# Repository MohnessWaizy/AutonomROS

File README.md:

# AutonomROS: Autonomous Car Swarm with Hardware-accelerated ROS Programming

## Paper @ IRC-2023:
[Paper: AutonomROS: A ReconROS-based Autonomonous Driving Unit](https://arxiv.org/pdf/2309.02026.pdf)

We present an Ackermann-based autonomous driving robot car based on  an [ROS 2](https://docs.ros.org/en/galactic/index.html) architecture alongside accelerated computationally intensive components using hardware acceleration through [ReconROS](https://github.com/Lien182/ReconROS) on an [Zynq UltraScale+ MPSoC ZCU104](https://www.xilinx.com/products/boards-and-kits/zcu104.html) FPGA board. First, our robot car can drive in a lane at a predefined speed. Second, it can detect obstacles and avoid collisions by stopping. Third, our car prevents intersection collisions with other vehicles by communicating via Wifi to a virtual traffic light offering smooth intersection coordination. Finally, since our developed architecture builds upon [Navigation 2 (Nav2)](https://navigation.ros.org/), a commonly used ROS 2 framework, we provide smooth integration and extendability. Furthermore, we accelerated three computationally intensive architecture components, lane detection, point cloud calculation, and obstacle detection, to save CPU time. In addition, we discovered that leveraging shared memory through [Iceoryx](https://iceoryx.io/latest/) as the ROS 2 middleware further reduced CPU time. Hence, we extended ReconROS’s capabilities by
making it compatible with Iceoryx.

<div align="center">
  
</div>

<div align="center">

</div>

<div align="center">

</div>

## Demo Video

<div align="center">
  
</div>

## Hardware

- Zynq UltraScale+ MPSoC ZCU104
- Traxxas Racecar Slash 2WD
- Ultrasonic Sensor (HC-SR04)
- Hall Sensor (KY-024)
- IMU (BNO055)
- PMOD0 Breakout Board
- 2D-Camera (SeeCam Cu30)
- 3D-Camera (Astra Pro)
- Wifi Sticks (TP Link TL-WN823NV3)
- Powered USB Hub (CSL USB Hub 3.2 Gen1)
- MakerBeams

## Tested on

- Ubuntu 20.04 LTS (Focal Fossa)
- ROS 2 Galactic
- Vivado 2021.2
- amd64 architecture (PC)
- arm64 architecture (ZCU104)

For more detailed information regarding dependencies consider the `ansible` folder

## Installation

### 0. Install git

If git is not already installed on your computer, install it with:

```bash
sudo apt install git
```

### 1. Clone the repository

```bash
git clone git@git.uni-paderborn.de:clienen/autonomros.git
```

### 2. Initialize the submodules

Change into the root of the repository and run the following command:

```bash
git submodule update --init
```

### 3. Initialize environment

We provide a recommended way to install all requirements using Ansible, which might cause changes on your system. Otherwise look into the ansible playbooks and follow the steps manually.

#### 3.1 Install Ansible

You can either run our script `first_install.sh` or look into the documentation of Ansible.
!We do not provide any warranty for potential damages!

```bash
ansible/scripts/first_install.sh
```

#### 3.2 Run Ansible

```bash
source ~/venvs/ansible/bin/activate
cd ansible/
ansible-playbook -i hosts.yml lab.yml -K --extra-vars "main_user_name=YOUR_USERNAME"
```

Exchange `YOUR_USERNAME` with your local username. It is required that you have root access via sudo. The `BECOME password` is your password. You may get an error for the `reconros : Build docker image` step. If this is the case, restart your computer and run the ansible playbook again.

#### 3.3 Install Vivado

Go to [Xilinx website](https://www.xilinx.com/support/download/index.html/content/xilinx/en/downloadNav/vivado-design-tools/2021-2.html) and download  Xilinx Unified Installer 2021.2: Linux Self Extracting Web Installer. Move the file into `~/ansible-files/`. Then run the following commands:

```bash
cd ~/ansible-files/
chmod u+x ./Xilinx_Unified_2021.2_1021_0703_Lin64.bin
./Xilinx_Unified_2021.2_1021_0703_Lin64.bin -- -b AuthTokenGen
```

Here, you will be asked for your Xilinx Account Credentials.
Next, you need to accept the Xilinx EULA and 3rd Party EULA.
The following command accepts the EULAs, downloads, and installs Vivado (this may take some hours):

```bash
~/ansible-files/Xilinx_Unified_2021.2_1021_0703_Lin64.bin -- -b Install -c ~/ansible-files/install_config.txt -a XilinxEULA,3rdPartyEULA
```

#### 3.4 Setup Virtual Traffic Light i.e. Installing mosquitto

To install the Mosquitto broker and the Mosquitto command line tools, run:

```bash
sudo apt-get install mosquitto mosquitto-clients -y
```

The Mosquitto broker starts automatically after installing.

Run the following line to start the Mosquitto broker on each system start:

```bash
sudo systemctl enable mosquitto
```

You need to allow anonymous acces by editing `/etc/mosquitto/mosquitto.conf` and adding:

```
allow_anonymous true
```

Be aware of the security implications!

The mosquitto server must be accessible by the board. You can listen on all interfaces by adding the following to the configuration.

```
listener 1883 0.0.0.0
```

Be aware of the security implications!

#### 3.5 Board Setup

You first need to setup an SD card. For this follow the steps in [board/README.md](board/README.md).

#### 3.6 Computer Setup

Append the following lines to your `.bashrc`:

```bash
source /opt/ros/galactic/setup.bash
export ROS_DOMAIN_ID=53
```

Reopen the terminal.

## Usage

### 1.1 Building the ReconROS project

Before running the commands below switch to the correct folder and source the ReconROS environment.

```bash
cd code/reconros_ws/carcontrol
source ../ReconROS/tools/settings.sh
```

Build the messages (Only necessary in the first setup)

```bash
make build-msg
```

Build the hardware. Make sure you have enough RAM or swap space (at least 32 GB combined are recommended).

```bash
make build-hw
```

Build the software

```bash
make build-sw
```

Copy the necessary files to the board

```bash
make copy
```

Note: Make sure to create an entry in your ssh config `~/.ssh/config` called `board` for the Zynq UltraScale+ MPSoC ZCU104

```bash
Host board
        User xilinx
        HostName BOARD_IP_ADDRESS
```

### 1.2 Building the ROS 2 packages

If you have previously performed the steps in the previous section, reopen the terminal to have a clean environment again.

```bash
cd code/ros_ws
```

Update `rosdep` with:

```bash
rosdep update --include-eol-distros
```

Install the required dependencies:

```bash
make dependencies
```

Build the ROS 2 packages for the board:

```bash
make build-arm64
```

Copy the necessary files to the board:

```bash
make board-copy
```

Update `rosdep` on the board:

```bash
ssh board rosdep update --include-eol-distros
```

Install the required dependencies on the board:

```bash
make board-dependencies
```

Copy the necessary scripts to the board:

```bash
cd code/scripts
make board-copy-scripts
```

### 2. Run with rviz2

Note: If anything crashes (except the `set_camera_config.sh`) rerun the step.

#### 2.1 Setup the rviz2 config

It is advised to use the config for rviz2 provided in [code/ros_ws/src/nav2_local/rviz/config.rviz](code/ros_ws/src/nav2_local/rviz/config.rviz)

Start rviz2 with

```bash
rviz2 -d code/ros_ws/src/nav2_local/rviz/config.rviz
```

#### 2.2 Connect to the board and start Roudi

Connect to the board

```bash
ssh board 
```

Run Roudi

```bash
./roudi.sh
```

#### 2.3 In a new terminal: Load the bitstream onto the FPGA and run the delegate threads

Connect to the board

```bash
ssh board 
```

Go in the directory `carcontrol`

```bash
cd carcontrol
```

Load the bitstream onto the FPGA

```bash
./load_fpga.sh
```

Run the delegate threads

```bash
sudo ./run_software.sh
```

#### 2.4 Start MQTT server for the virtual traffic light

Make sure the MQTT server is running on the computer:

```bash
service mosquitto status
```

#### 2.5 In a new terminal: Start Nav2

Connect to the board

```bash
ssh board
```

Run Nav2

```bash
sudo ./start_nav2.sh
```

Important: Wait until the terminal stops outputting log messages

#### 2.6 In a new terminal: Configure the 2D camera

Connect to the board

```bash
ssh board
```

Run the configuration file

```bash
./set_camera_config.sh
```

Wait approximately 5 seconds and rerun the command:

```bash
./set_camera_config.sh
```

Go back to rviz2 on your local machine and press "Startup" and wait until the terminal running Nav2 stops outputting log messages again. In rvz2 the car and the costmap should be visible at this point.

#### 2.7 In a new terminal: Start the 3D camera

Connect to the board

```bash
ssh board
```

Activate the 3D camera

```bash
./activate.sh
```

Finally you can set a goal pose in rviz2 and the car should start driving towards the goal.

### 3. Run with Wifi

Note: If you experience issues running ROS 2 over WiFi. Please consider the following steps:

- Often you cannot use rviz2 via WiFi
- Start Nav2 with `start_nav2_wifi.sh` instead of `start_nav2.sh` to automatically startup Nav2
- Specify goal poses through the topic `/goal_pose` instead of using rviz2 GUI.

## Contributors

All members contributed equally. Hence, the members are listed in alphabetical order.

| Contributor |  Email |
|---|---|
| Mathis Brede B.Sc. | <mbrede@mail.upb.de> |
| Daniel Karger B.Sc. | <dkarger@mail.upb.de> |
| Kevin Koch B.Sc. | <kevink2@mail.upb.de> |
| Dalisha Logan B.Sc. | <dalisha@mail.upb.de> |
| Janet Mazur B.Sc. | <mazurj@mail.upb.de> |
| Alexander Nowosad B.Sc. | <anowosad@mail.upb.de> |
| Alexander Schnelle B.Sc. | <aschnell@mail.upb.de> |
| Mohness Waizy B.Sc. (Team leader)| <waizy@mail.upb.de> |

| Supervisor |  Email |
|---|---|
| Prof. Dr. Marco Platzner  | <platzner@upb.de> |
| Christian Lienen, M.Sc. | <christian.lienen@upb.de> |

## Acknowledgment

We especially thank Prof. Dr. Marco Platzner and Christian Lienen for allowing us to work on an exciting project group involving autonomous driving and hardware acceleration. Moreover, we are thankful for the excellent working conditions in the lab provided
to us. We would like to thank Christian Lienen for his continuous support and trust through-out the project. Furthermore, we would also like to thank Andre Diekwisch and Torben Gotowik, who have been available to support us with any administrative and equipment
needs. Also, we would like to thank Lennart Clausing and Felix Jentzsch for their guidance and support regarding hardware-related issues. Additionally, we thank Elisabeth Schlatt for her assistance with any administrative questions we had. Furthermore, we would like to sincerely thank Prof. Dr. Marco Platzner and the entire working group for giving us the opportunity to participate in this year’s seminar-workshop. It has been a very enjoyable and inspiring experience.
Finally, we would like to thank the entire working group and all those who have helped us in any way to bring the project forward. Your support and contributions were valuable to the success of our project.

## License

For open source projects, say how it is licensed.

## Project status

This project was actively developed and maintained from April 2022 to March 2023. Development has since been terminated, but we will strive to provide support and address any issues that may arise in the future.

If you encounter any bugs or issues with the project, please don't hesitate to file an issue on our GitHub repository. While we may not be actively developing new features for the project, we will do our best to provide timely assistance and bug fixes.

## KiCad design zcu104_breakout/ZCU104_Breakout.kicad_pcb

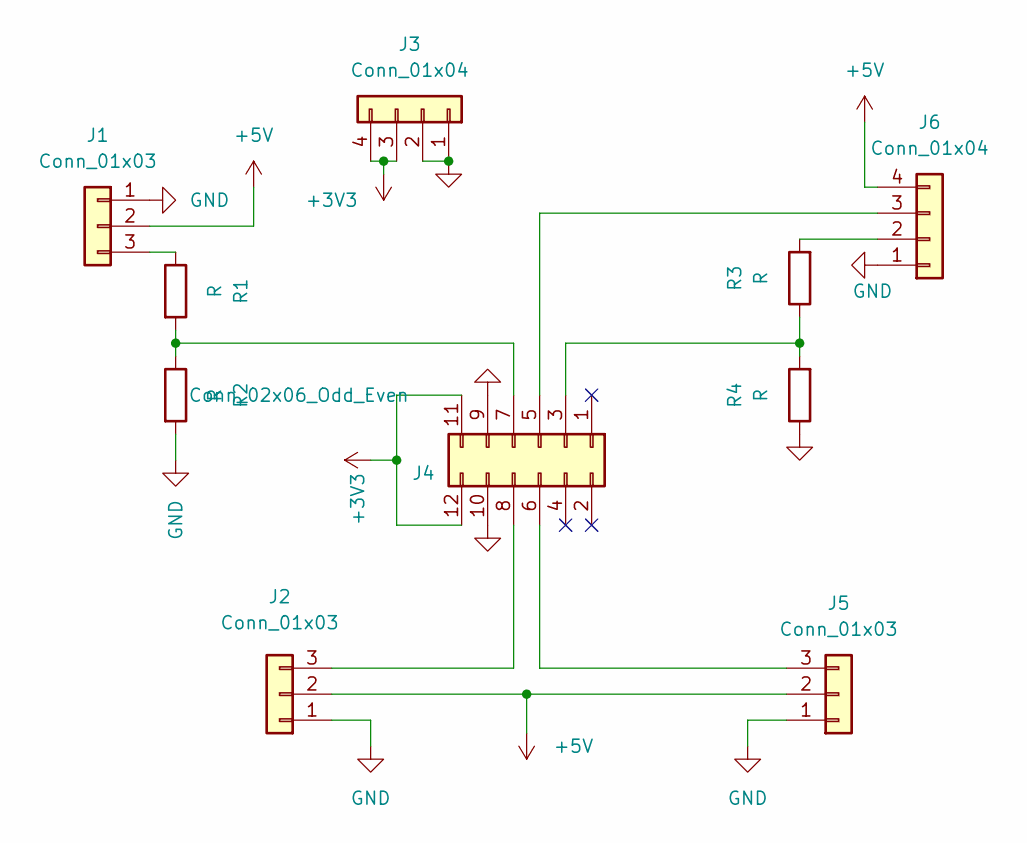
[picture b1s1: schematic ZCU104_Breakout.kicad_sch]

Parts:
J1, J2, J5: Conn_01x03; PinHeader_1x03_P2.54mm_Horizontal
J3, J6: Conn_01x04; PinHeader_1x04_P2.54mm_Horizontal
J4: Conn_02x06_Odd_Even; PinHeader_2x06_P2.54mm_Vertical
R1, R2, R3, R4: R; R_0805_2012Metric_Pad1.20x1.40mm_HandSolder

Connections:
+3V3: J3.3, J3.4, J4.11, J4.12
+5V: J1.2, J2.2, J5.2, J6.4
GND: J1.1, J2.1, J3.1, J3.2, J4.9, J4.10, J5.1, J6.1, R2.2, R4.1
unnamed: J1.3, R1.1
unnamed: J2.3, J4.8
unnamed: J4.6, J5.3
unnamed: J6.2, R3.2
unnamed: J4.5, J6.3
unnamed: J4.7, R1.2, R2.1
unnamed: J4.3, R3.1, R4.2

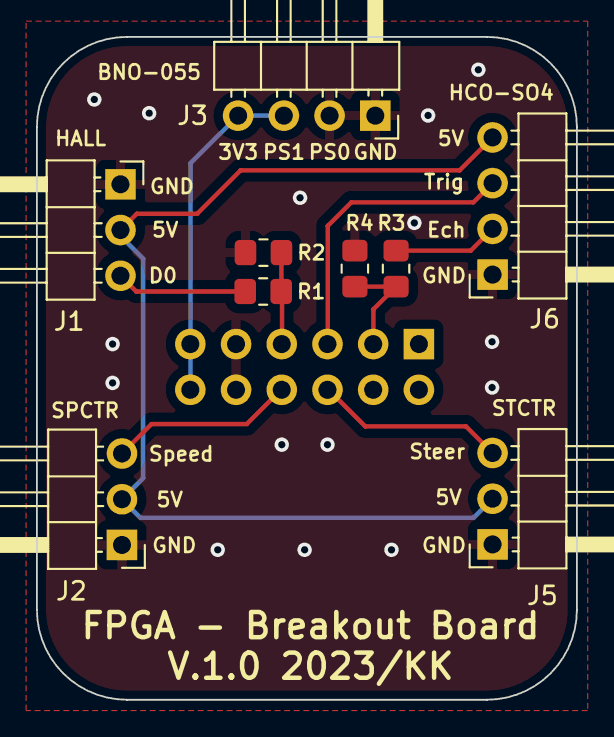
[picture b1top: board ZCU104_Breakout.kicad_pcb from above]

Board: 2 copper layers, 30.0 x 36.8 mm, 10 parts (1 on the bottom side), 10 nets.

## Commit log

2023-11-04 Init
2023-11-04 hotfix
2023-11-04 add paper
